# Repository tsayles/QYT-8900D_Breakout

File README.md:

# QYT-8900D AOC Interface Research Platform

## Overview

This project has evolved from a simple microphone interface breakout into a more ambitious radio signal research platform. The current goal is to build a man-in-the-middle device using the N6AD AOC circuit concept as a foundation for reverse engineering the microphone interface and exploring radio control behavior.

The design is intended to sit in-line between a handheld microphone and the radio, or between an external audio source and the microphone input, allowing observation, capture, and controlled manipulation of microphone audio and associated control lines.

## New project goals

1. Leverage the N6AD AOC circuitry as a reference architecture for audio and control interface monitoring.
2. Build a man-in-the-middle adapter to observe and capture microphone audio without permanently altering the radio or microphone.
3. Reverse engineer the QYT microphone interface behavior and signal conventions.
4. Identify and document the audio path, PTT handling, and microphone ground/line control relationships.
5. Explore the feasibility of implementing basic CAT control or remote radio control functions through the same interface concepts.
6. Use the project as a practical platform for learning serial/control signaling, mic ICD analysis, and radio hardware experimentation.

## Why this direction

The original breakout board idea was useful for simple recording and interface convenience. The current direction shifts toward deeper radio analysis and experimentation:

- microphone ICD reverse engineering
- signal tracing across the hand mic and radio side
- controlled insertion of test equipment or analysis hardware
- investigation of AOC-style control ideas for practical ham radio experimentation

This makes the board more than just a passive adapter: it becomes a research and test fixture for disciplined signal analysis.

## Intended functionality

The revised design should support the following concepts:

- Passive or buffered insertion between the microphone and the radio
- Access to microphone audio, PTT, ground, and auxiliary lines
- Recording or monitoring of audio on the mic path
- Ability to inject test audio or simulate microphone behavior
- Optional control line observation and experimentation
- A platform for testing CAT-like control ideas in a controlled environment

## Relationship to the original board

The original QYT-8900D breakout board was a straightforward pass-through interface with RJ-45 and phone-jack access for recording and testing. That original concept remains historically relevant, but the current direction reuses the same general spirit of interface access while adding a much more analytical and experimental purpose.

The older design remains as a reference for the board's original telemetry and breakout organization, while the new work focuses on:

- signal-level investigation
- interface documentation
- non-destructive testing on live radio hardware
- process-oriented reverse engineering

## Research and experimentation focus

This project is intended to serve as a practical platform for:

- tracing microphone signal paths
- measuring audio voltage levels and biasing
- observing switch and control line behavior
- testing AOC-derived circuit ideas in real hardware
- studying basic CAT control interfaces for a transceiver

## Safety and scope

This project is experimental and intended for low-voltage signal-level work only. It is not designed for direct high-power or hazardous RF modifications. The board is best used as a measurement and analysis tool for lab or bench work.

## Notes

This README reflects the current project direction and supersedes the earlier, simpler breakout-board description. The original revision-based historical documentation remains available in the dated archive files for reference.

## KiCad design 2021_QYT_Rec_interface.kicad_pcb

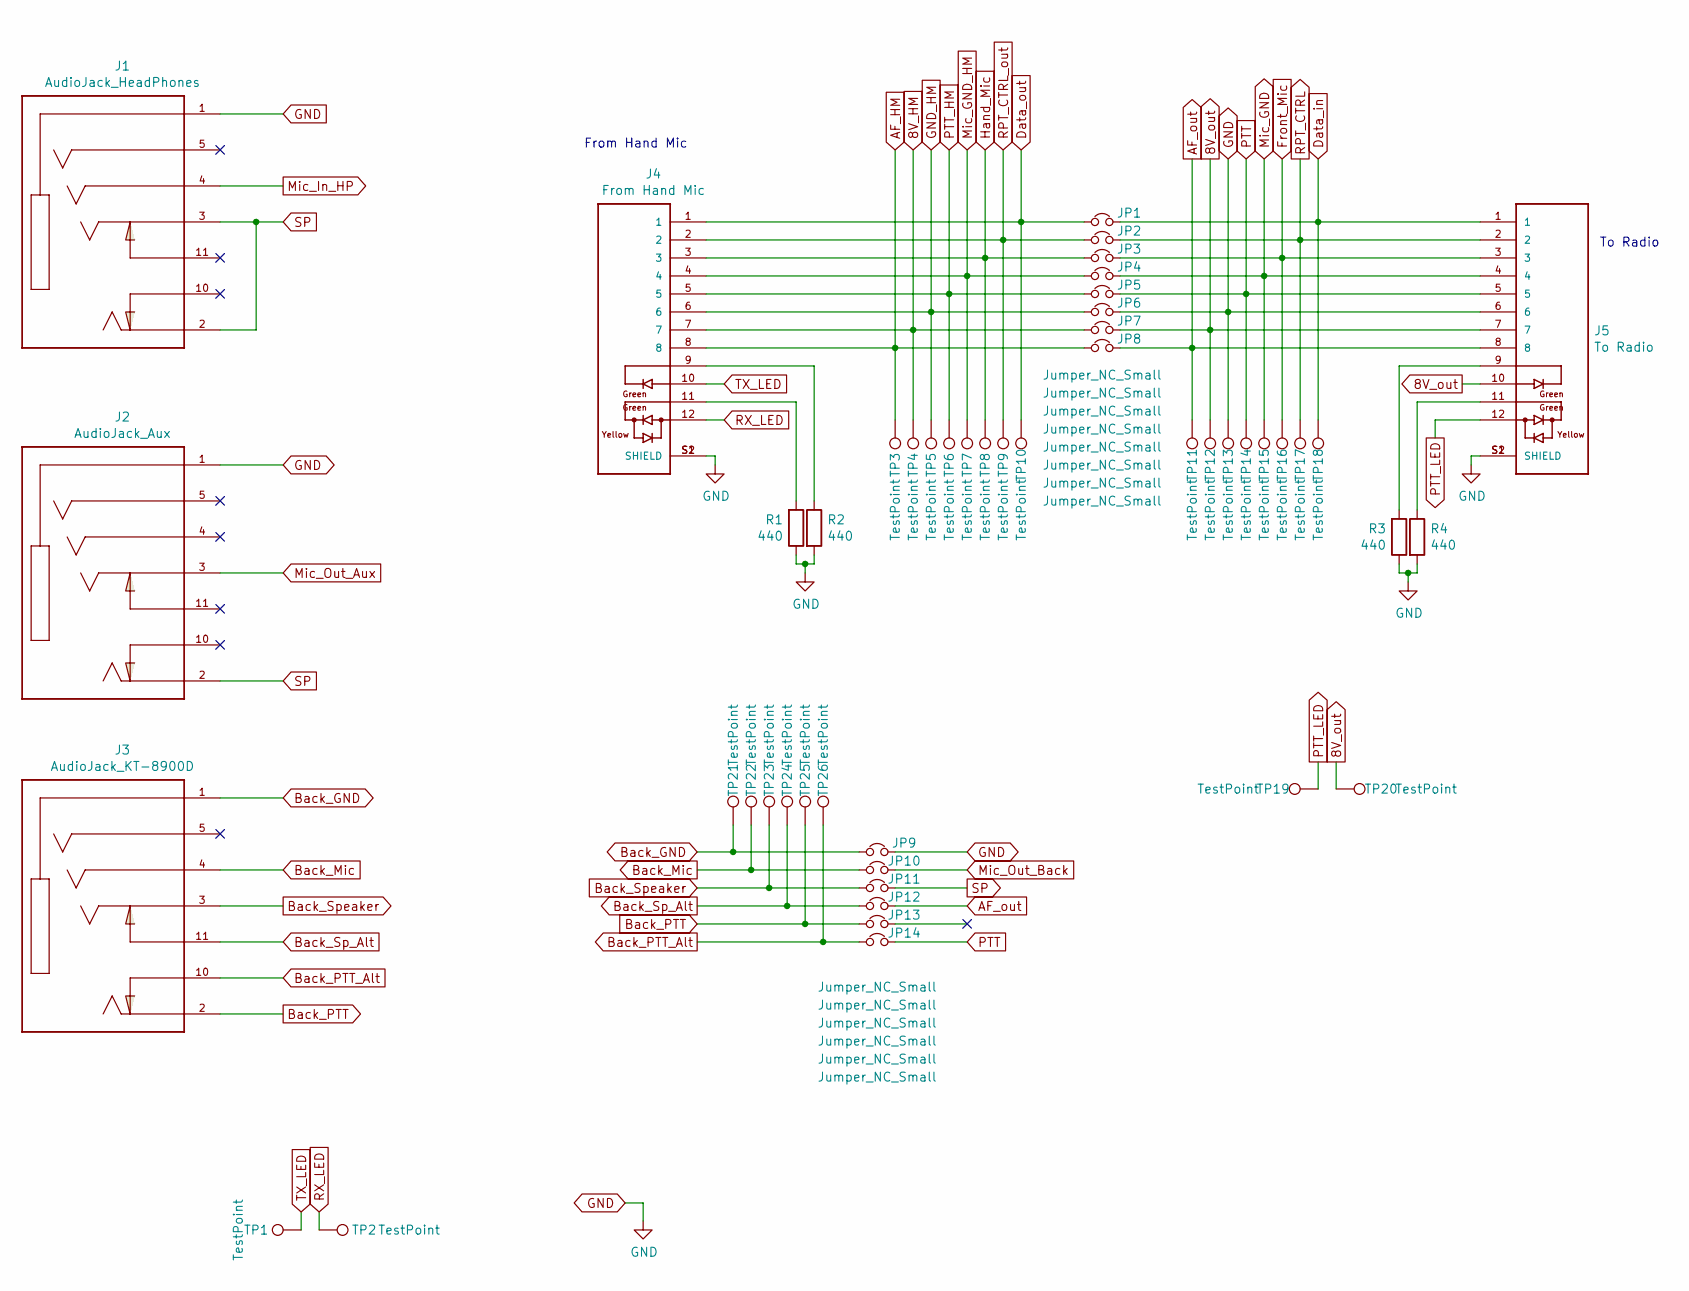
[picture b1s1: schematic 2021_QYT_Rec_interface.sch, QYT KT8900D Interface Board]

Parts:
J1: AudioJack_HeadPhones; CUI_SJ2-35825D-SMT-TR; MPN SJ2-35825D-SMT-TR
J2: AudioJack_Aux; CUI_SJ2-35825D-SMT-TR; MPN SJ2-35825D-SMT-TR
J3: AudioJack_KT-8900D; CUI_SJ2-35825D-SMT-TR; MPN SJ2-35825D-SMT-TR
J4: From Hand Mic; TE_2041411-1
J5: To Radio; TE_2041411-1
JP1, JP2, JP3, JP4, JP5, JP6, JP7, JP8, JP9, JP10, JP11, JP12, JP13, JP14: Jumper_NC_Small; SolderJumper-2_P1.3mm_Bridged_Pad1.0x1.5mm
R1, R2, R3, R4: 440; R_Axial_DIN0207_L6.3mm_D2.5mm_P10.16mm_Horizontal
TP1, TP2, TP3, TP4, TP5, TP6, TP7, TP8, TP9, TP10, TP11, TP12, TP13, TP14, TP15, TP16, TP17, TP18, TP19, TP20, TP21, TP22, TP23, TP24, TP25, TP26: TestPoint; TestPoint_Loop_D2.50mm_Drill1.0mm

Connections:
8V_HM: J4.7, JP7.1, TP4.1
8V_out: J5.7, J5.10, JP7.2, TP12.1, TP20.1
AF_HM: J4.8, JP8.1, TP3.1
AF_out: J5.8, JP8.2, JP12.2, TP11.1
Back_GND: J3.1, JP9.1, TP21.1
Back_Mic: J3.4, JP10.1, TP22.1
Back_PTT: J3.2, JP13.1, TP25.1
Back_PTT_Alt: J3.10, JP14.1, TP26.1
Back_Sp_Alt: J3.11, JP12.1, TP24.1
Back_Speaker: J3.3, JP11.1, TP23.1
Data_in: J5.1, JP1.2, TP18.1
Data_out: J4.1, JP1.1, TP10.1
Front_Mic: J5.3, JP3.2, TP16.1
GND: J1.1, J2.1, J4.S1 (SHIELD), J4.S2 (SHIELD), J5.6, J5.S1 (SHIELD), J5.S2 (SHIELD), JP6.2, JP9.2, R1.1, R2.2, R3.1, R4.2, TP13.1
GND_HM: J4.6, JP6.1, TP5.1
Hand_Mic: J4.3, JP3.1, TP8.1
Mic_GND: J5.4, JP4.2, TP15.1
Mic_GND_HM: J4.4, JP4.1, TP7.1
Mic_In_HP: J1.4
Mic_Out_Aux: J2.3
Mic_Out_Back: JP10.2
unnamed: J4.9, R2.1
unnamed: J4.11, R1.2
unnamed: J5.9, R3.2
unnamed: J5.11, R4.1
PTT: J5.5, JP5.2, JP14.2, TP14.1
PTT_HM: J4.5, JP5.1, TP6.1
PTT_LED: J5.12, TP19.1
RPT_CTRL: J5.2, JP2.2, TP17.1
RPT_CTRL_out: J4.2, JP2.1, TP9.1
RX_LED: J4.12, TP2.1
SP: J1.2, J1.3, J2.2, JP11.2
TX_LED: J4.10, TP1.1

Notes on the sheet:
To Radio
From Hand Mic

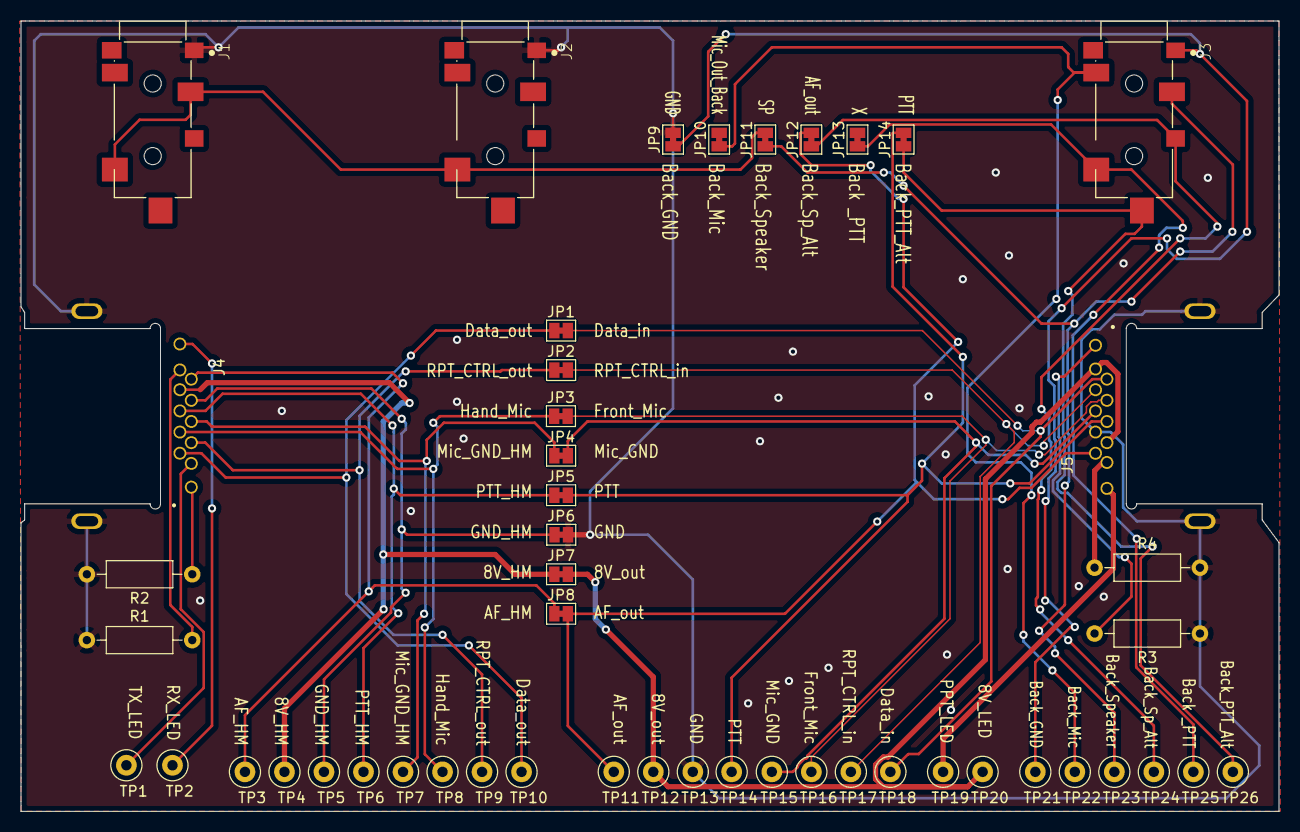
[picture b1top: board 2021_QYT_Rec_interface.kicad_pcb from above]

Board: 2 copper layers, 121.3 x 76.2 mm, 49 parts (0 on the bottom side), 30 nets.

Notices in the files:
2021_QYT_Rec_interface.kicad_pcb:
Creative Commons, Attribution & Share Alike
https://creativecommons.org/licenses/by-sa/3.0
